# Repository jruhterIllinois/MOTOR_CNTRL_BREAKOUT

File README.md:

# MOTOR_CNTRL_BREAKOUT
Hardware Design for a motor contol breakout board to hold LDE 220 cannon scanner head

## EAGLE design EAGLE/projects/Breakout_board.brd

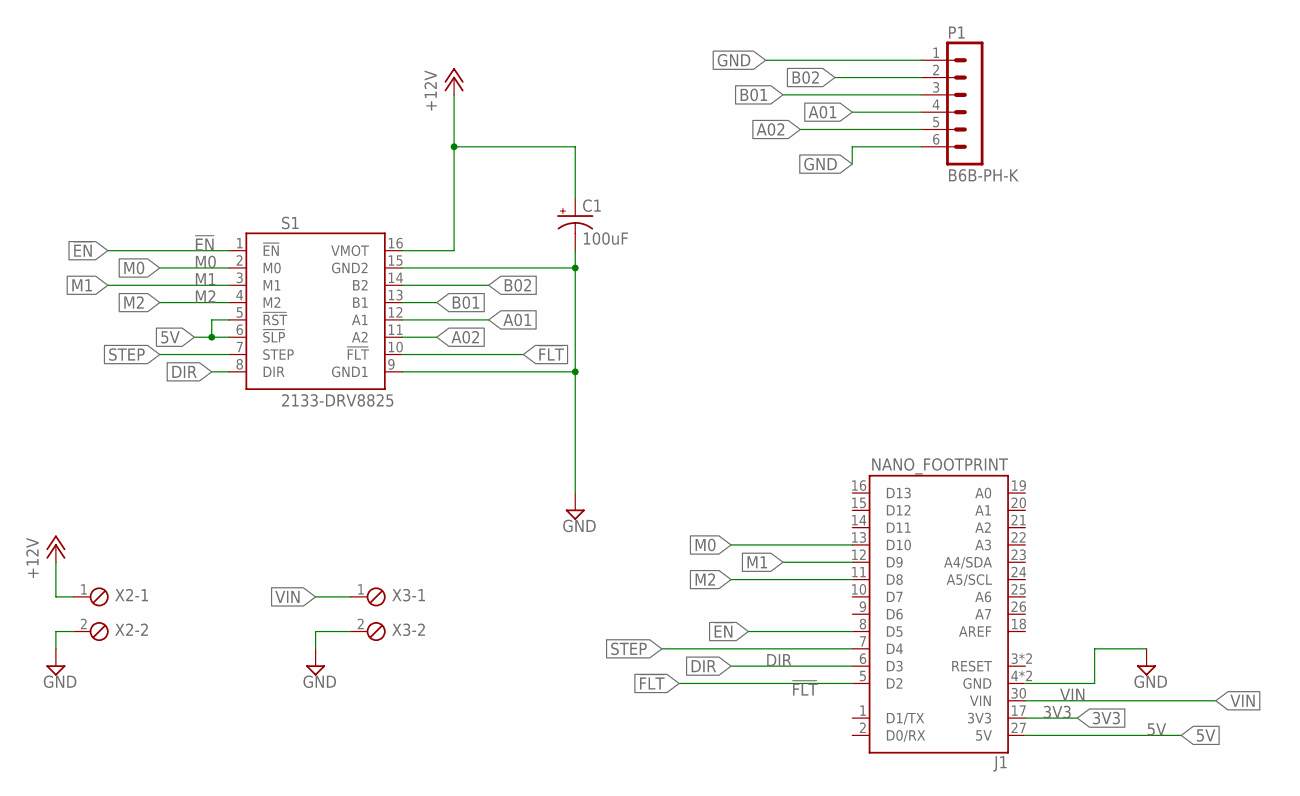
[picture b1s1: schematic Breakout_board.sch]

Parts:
C1: 100uF; EIA7343
J1: NANO_FOOTPRINT; NANO
P1: B6B-PH-K
S1: 2133-DRV8825; DRV8825
X2, X3: MPT2; 2POL254

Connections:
3V3: J1.17 (3V3)
5V: J1.27 (5V), S1.5 (!RST), S1.6 (!SLP)
!EN: J1.8 (D5), S1.1 (!EN)
!FLT: J1.5 (D2), S1.10 (!FLT)
+12V: C1.A (+), S1.16 (VMOT), X2.1
A01: P1.4, S1.12 (A1)
A02: P1.5, S1.11 (A2)
B01: P1.3, S1.13 (B1)
B02: P1.2, S1.14 (B2)
DIR: J1.6 (D3), S1.8 (DIR)
GND: C1.C (-), J1.4 (GND), J1.29 (GND), P1.1, P1.6, S1.9 (GND1), S1.15 (GND2), X2.2, X3.2
M0: J1.13 (D10), S1.2 (M0)
M1: J1.12 (D9), S1.3 (M1)
M2: J1.11 (D8), S1.4 (M2)
STEP: J1.7 (D4), S1.7 (STEP)
VIN: J1.30 (VIN), X3.1

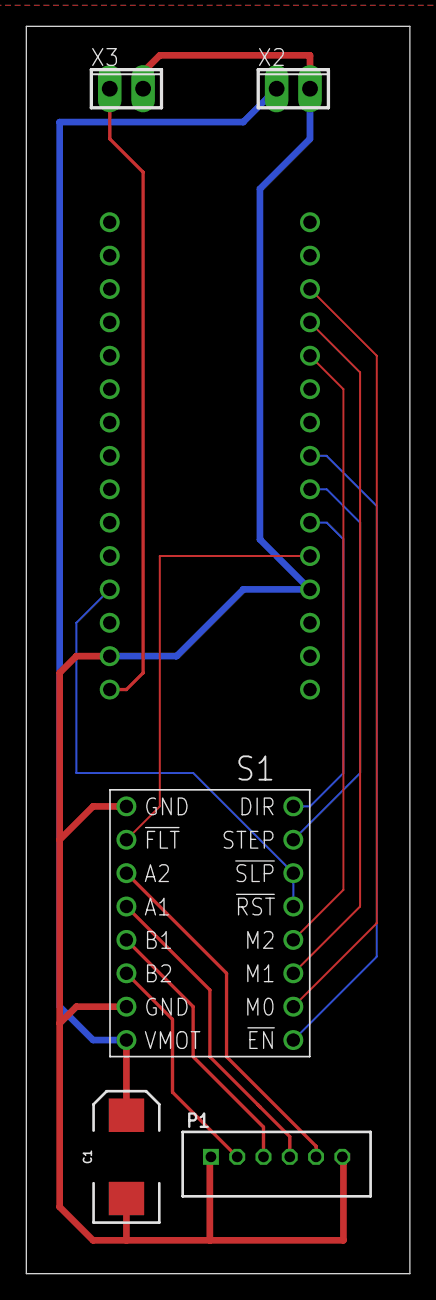
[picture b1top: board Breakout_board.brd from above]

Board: 2 copper layers, 29.2 x 94.9 mm, 6 parts (0 on the bottom side), 15 nets.

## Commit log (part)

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2026-02-27 Initial check in for eagle fills
2026-04-21 Add files via upload
    Mechanical Design Files

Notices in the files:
parts and their libraries:
SparkFun-Capacitors: Licensing: Creative Commons ShareAlike 4.0 International - https://creativecommons.org/licenses/by-sa/4.0
con-jst-ph: Copyright (C) 2016, Bob Starr
